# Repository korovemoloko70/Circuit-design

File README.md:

# Circuit-design
my projects for 2024-2025

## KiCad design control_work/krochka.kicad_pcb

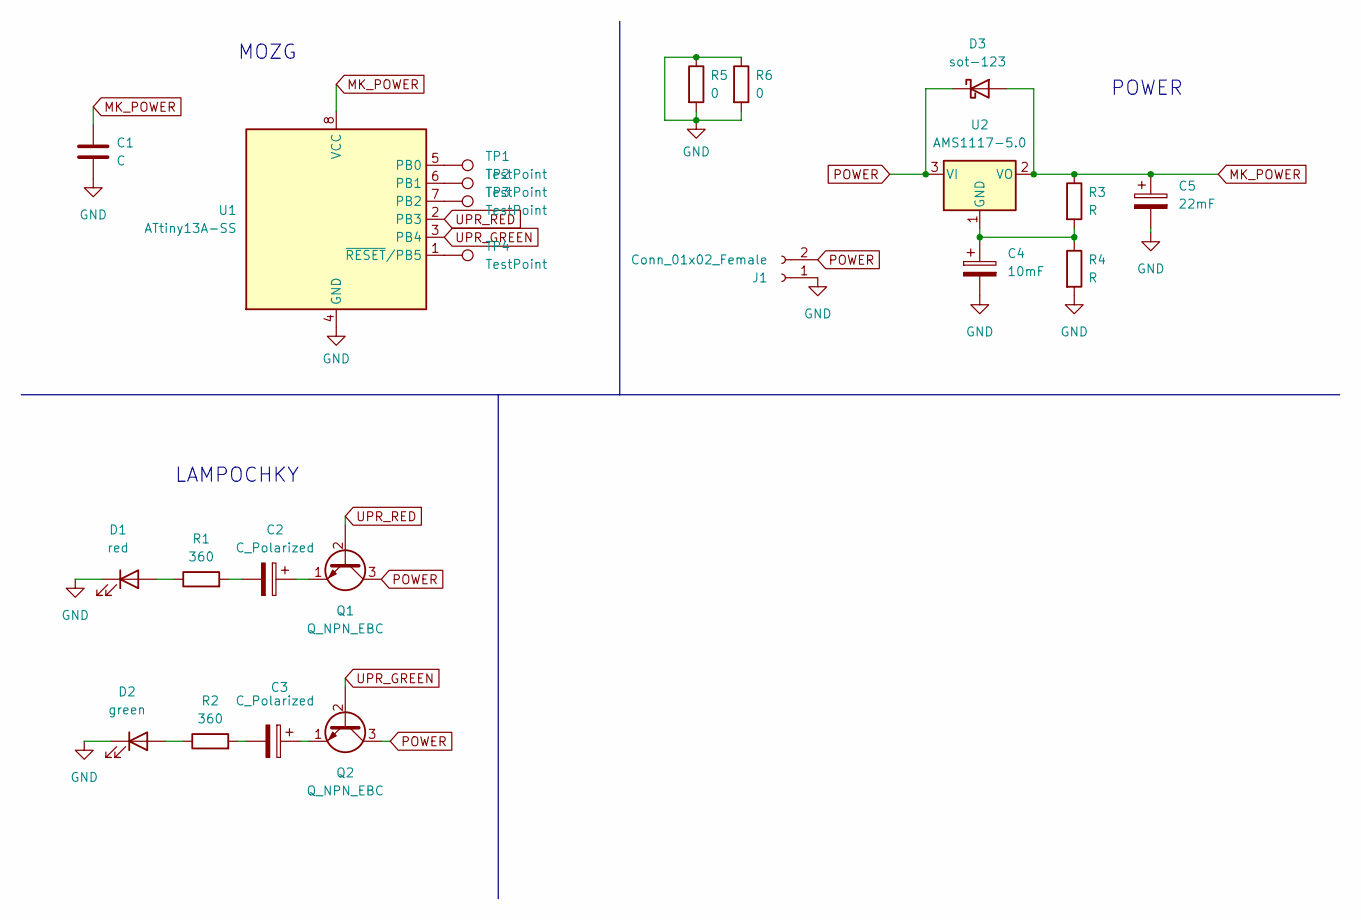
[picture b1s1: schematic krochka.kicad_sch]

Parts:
C1: C; CP_Elec_4x3
C2, C3: C_Polarized; CP_EIA-3528-21_Kemet-B
C4: 10mF; CP_EIA-3528-21_Kemet-B
C5: 22mF; CP_EIA-3528-21_Kemet-B
D1: red; LED_D5.0mm
D2: green; LED_D5.0mm
D3: sot-123; D_0201_0603Metric_Pad0.64x0.40mm_HandSolder
J1: Conn_01x02_Female; PinSocket_1x02_P2.00mm_Vertical
Q1, Q2: Q_NPN_EBC; SOT-23
R1, R2: 360; R_0402_1005Metric_Pad0.72x0.64mm_HandSolder
R3, R4: R; R_0402_1005Metric_Pad0.72x0.64mm_HandSolder
R5, R6: 0; R_0603_1608Metric
TP1, TP2, TP3, TP4: TestPoint; TestPoint_Pad_D1.5mm
U1: ATtiny13A-SS; SOIC-8_3.9x4.9mm_P1.27mm
U2: AMS1117-5.0; SOT-223-3_TabPin2

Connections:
GND: C1.2, C4.2, C5.2, D1.1 (K), D2.1 (K), J1.1, R4.2, R5.1, R5.2, R6.1, R6.2, U1.4 (GND)
MK_POWER: C1.1, C5.1, D3.2 (A), R3.1, U1.8 (VCC), U2.2 (VO)
unnamed: C2.1, Q1.1 (E)
unnamed: C2.2, R1.2
unnamed: C3.1, Q2.1 (E)
unnamed: C3.2, R2.2
unnamed: C4.1, R3.2, R4.1, U2.1 (GND)
unnamed: D1.2 (A), R1.1
unnamed: D2.2 (A), R2.1
unnamed: TP1.1, U1.5 (PB0)
unnamed: TP2.1, U1.6 (PB1)
unnamed: TP3.1, U1.7 (PB2)
unnamed: TP4.1, U1.1 (~RESET/PB5)
POWER: D3.1 (K), J1.2, Q1.3 (C), Q2.3 (C), U2.3 (VI)
UPR_GREEN: Q2.2 (B), U1.3 (PB4)
UPR_RED: Q1.2 (B), U1.2 (PB3)

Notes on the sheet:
POWER
MOZG
LAMPOCHKY

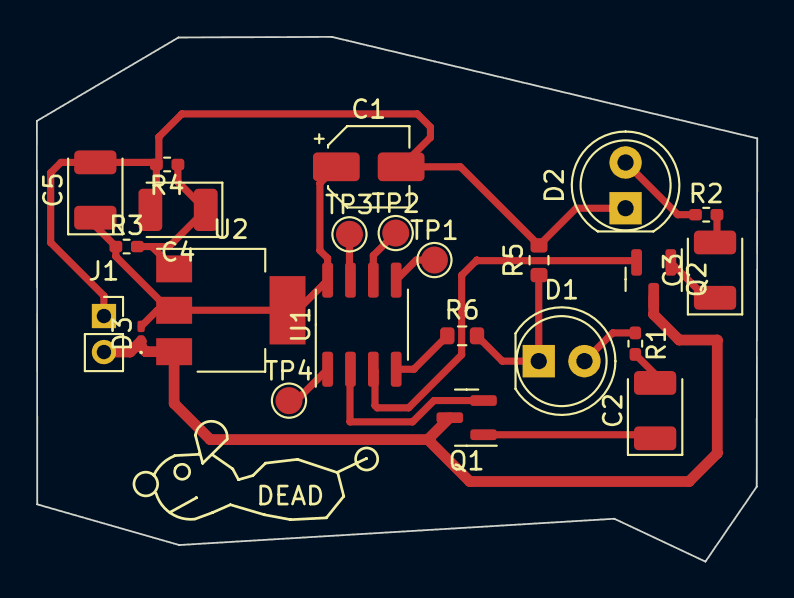
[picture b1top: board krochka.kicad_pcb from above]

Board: 2 copper layers, 40.0 x 29.2 mm, 23 parts (0 on the bottom side), 16 nets.

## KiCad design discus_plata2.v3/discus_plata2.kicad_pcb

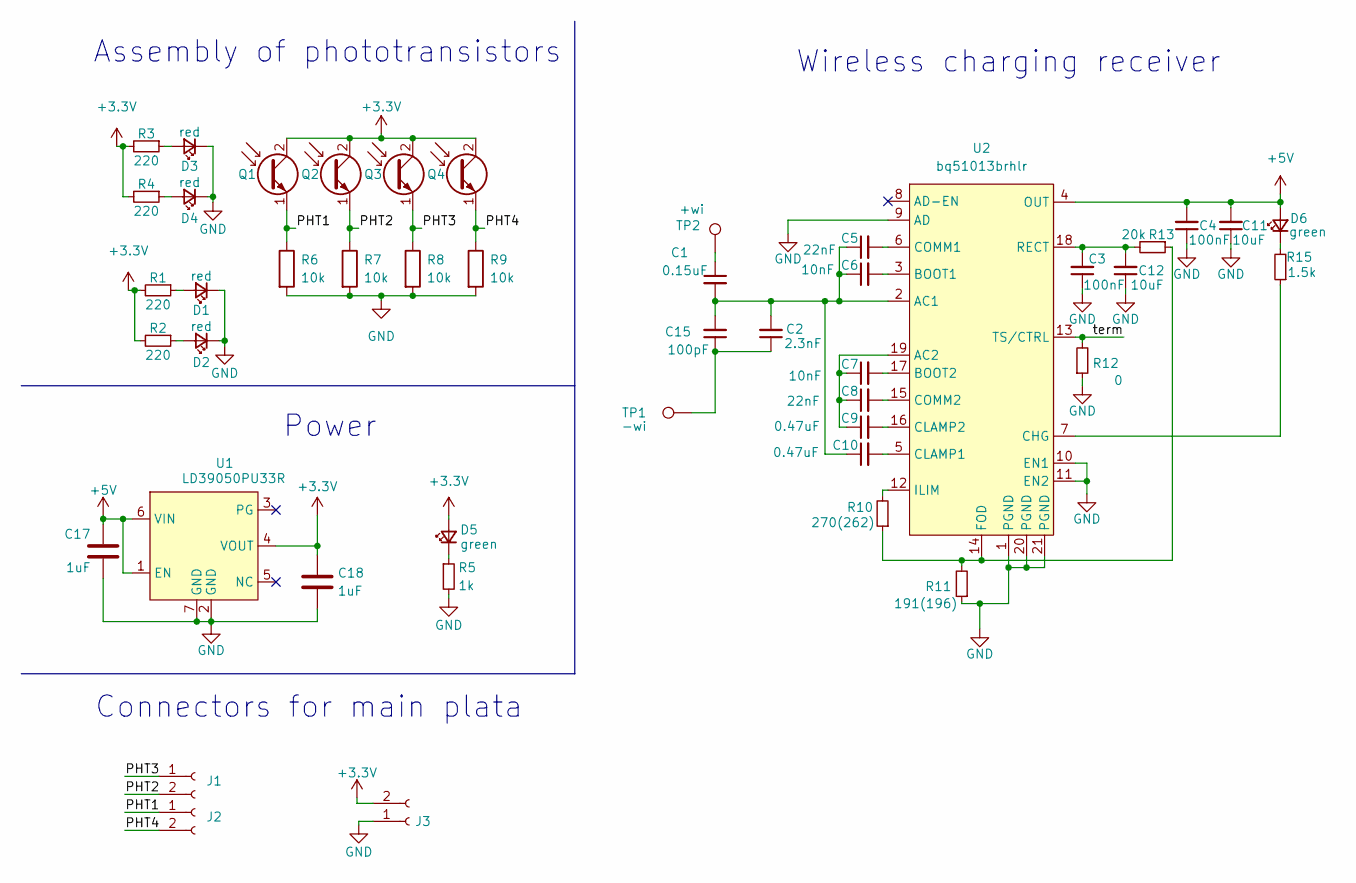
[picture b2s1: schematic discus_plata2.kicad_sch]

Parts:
C1: 0.15uF; C_0402_1005Metric_Pad0.74x0.62mm_HandSolder
C2: 2.3nF; C_0402_1005Metric_Pad0.74x0.62mm_HandSolder
C3, C4: 100nF; C_0201_0603Metric_Pad0.64x0.40mm_HandSolder
C5, C8: 22nF; C_0402_1005Metric_Pad0.74x0.62mm_HandSolder
C6, C7: 10nF; C_0402_1005Metric_Pad0.74x0.62mm_HandSolder
C9, C10: 0.47uF; C_0402_1005Metric_Pad0.74x0.62mm_HandSolder
C11, C12: 10uF; C_0402_1005Metric_Pad0.74x0.62mm_HandSolder
C15: 100pF; C_0402_1005Metric_Pad0.74x0.62mm_HandSolder
C17, C18: 1uF; C_0402_1005Metric_Pad0.74x0.62mm_HandSolder
D1, D2, D3, D4: red; LED_0603_1608Metric_Pad1.05x0.95mm_HandSolder
D5, D6: green; LED_0603_1608Metric_Pad1.05x0.95mm_HandSolder
J1, J2, J3: B2B-ZR
Q1, Q2, Q3, Q4: Q_Photo_NPN_EC; R_1206_3216Metric_Pad1.30x1.75mm_HandSolder
R1, R2, R3, R4: 220; R_0603_1608Metric_Pad0.98x0.95mm_HandSolder
R5: 1k; R_0402_1005Metric_Pad0.72x0.64mm_HandSolder
R6, R7, R8, R9: 10k; R_0402_1005Metric_Pad0.72x0.64mm_HandSolder
R10: 270(262); R_0402_1005Metric_Pad0.72x0.64mm_HandSolder
R11: 191(196); R_0402_1005Metric_Pad0.72x0.64mm_HandSolder
R12: 0; R_0201_0603Metric_Pad0.64x0.40mm_HandSolder
R13: 20k; R_0402_1005Metric_Pad0.72x0.64mm_HandSolder
R15: 1.5k; R_0402_1005Metric_Pad0.72x0.64mm_HandSolder
TP1: -wi; WICH_TESTP
TP2: +wi; WICH_TESTP
U1: LD39050PU33R; DFN-6-1EP_3x3mm_P0.95mm_EP1.7x2.6mm
U2: bq51013brhlr; Texas_VQFN-RHL-20

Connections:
+3.3V: C18.1, D5.2 (A), J3.2, Q1.2 (C), Q2.2 (C), Q3.2 (C), Q4.2 (C), R1.2, R2.2, R3.2, R4.2, U1.4 (VOUT)
+5V: C4.2, C11.2, C17.1, D6.2 (A), U1.1 (EN), U1.6 (VIN), U2.4 (OUT)
/PHT1: J2.1, Q1.1 (E), R6.1
/PHT2: J1.2, Q2.1 (E), R7.1
/PHT3: J1.1, Q3.1 (E), R8.1
/PHT4: J2.2, Q4.1 (E), R9.1
/term: R12.2, U2.13 (TS/CTRL)
GND: C3.1, C4.1, C11.1, C12.1, C17.2, C18.2, D1.1 (K), D2.1 (K), D3.1 (K), D4.1 (K), J3.1, R5.2, R6.2, R7.2, R8.2, R9.2, R11.1, R12.1, U1.2 (GND), U1.7 (GND), U2.1 (PGND), U2.9 (AD), U2.10 (EN1), U2.11 (EN2), U2.20 (PGND), U2.21 (PGND)
unnamed: C1.1, TP2.1
unnamed: C2.1, C15.1, TP1.1
unnamed: D1.2 (A), R1.1
unnamed: D2.2 (A), R2.1
unnamed: D3.2 (A), R3.1
unnamed: D4.2 (A), R4.1
unnamed: D5.1 (K), R5.1
unnamed: D6.1 (K), R15.2
unnamed: C1.2, C2.2, C5.1, C6.1, C10.1, C15.2, U2.2 (AC1)
unnamed: C7.1, C8.1, C9.1, U2.19 (AC2)
unnamed: C6.2, U2.3 (BOOT1)
unnamed: C7.2, U2.17 (BOOT2)
unnamed: R15.1, U2.7 (CHG)
unnamed: C10.2, U2.5 (CLAMP1)
unnamed: C9.2, U2.16 (CLAMP2)
unnamed: C5.2, U2.6 (COMM1)
unnamed: C8.2, U2.15 (COMM2)
unnamed: R10.1, R11.2, R13.1, U2.14 (FOD)
unnamed: R10.2, U2.12 (ILIM)
unnamed: C3.2, C12.2, R13.2, U2.18 (RECT)

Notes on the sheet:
Connectors for main plata
Assembly of phototransistors
Wireless charging receiver
Power

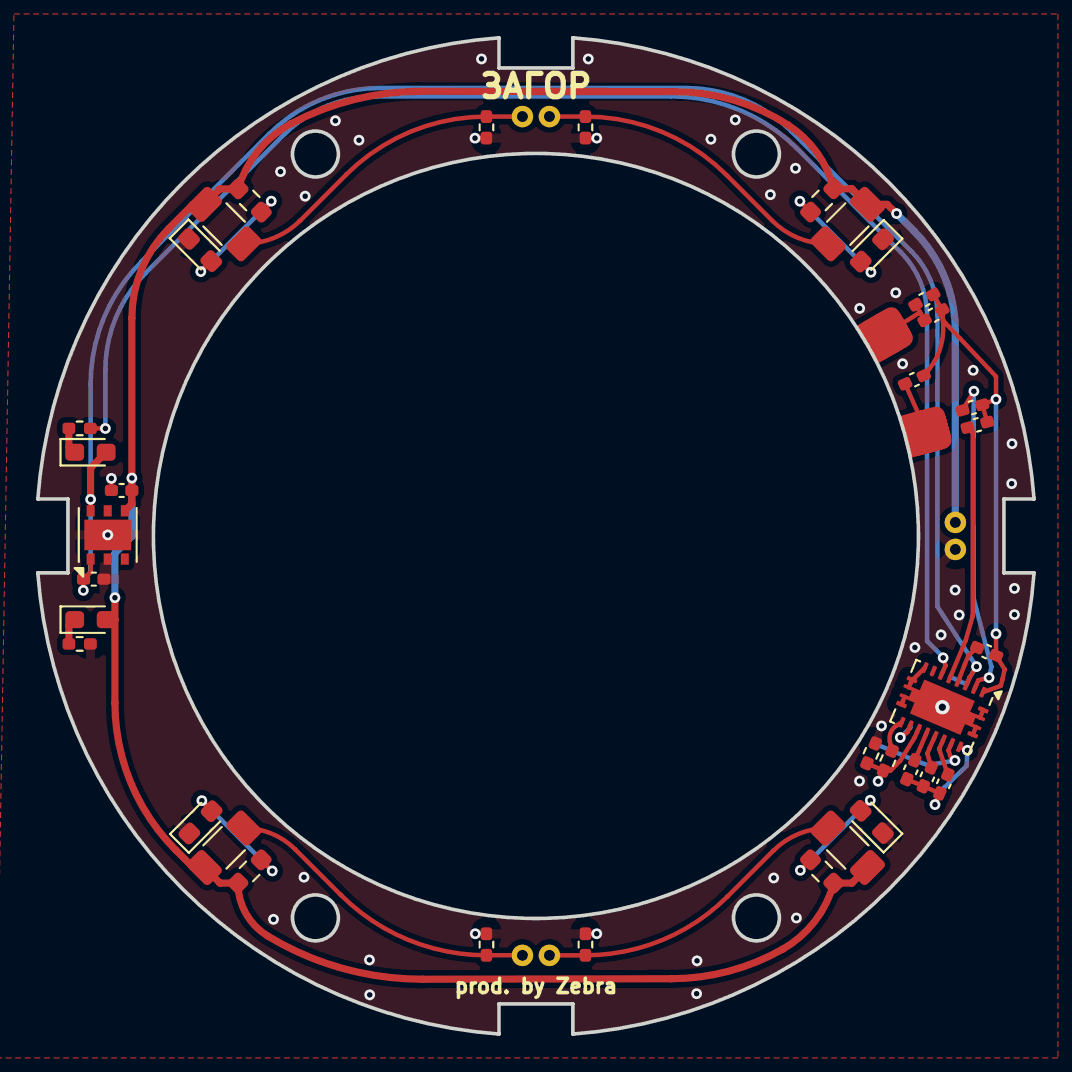
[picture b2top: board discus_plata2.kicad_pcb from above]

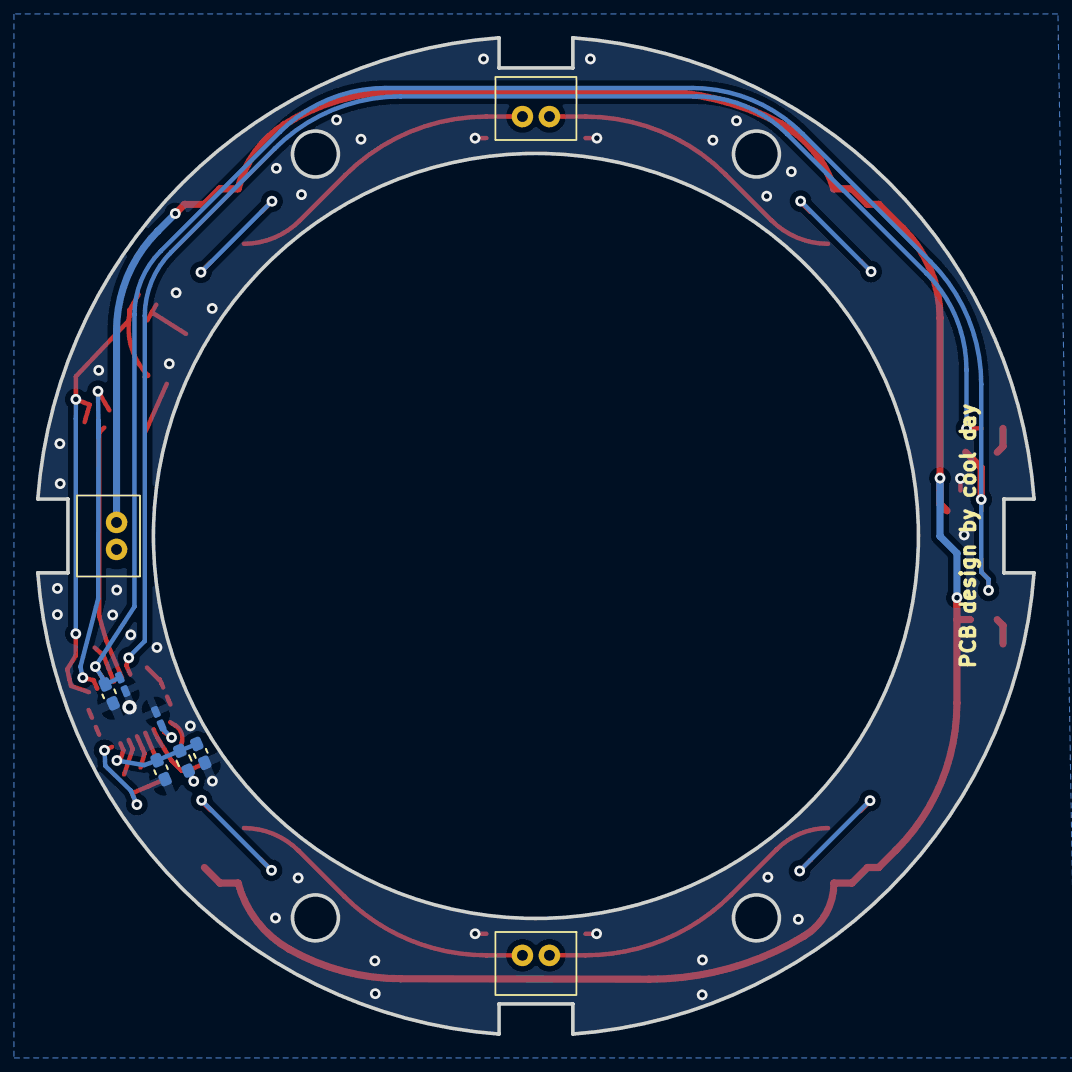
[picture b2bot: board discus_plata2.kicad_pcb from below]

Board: 2 copper layers, 55.3 x 55.3 mm, 46 parts (9 on the bottom side), 28 nets.

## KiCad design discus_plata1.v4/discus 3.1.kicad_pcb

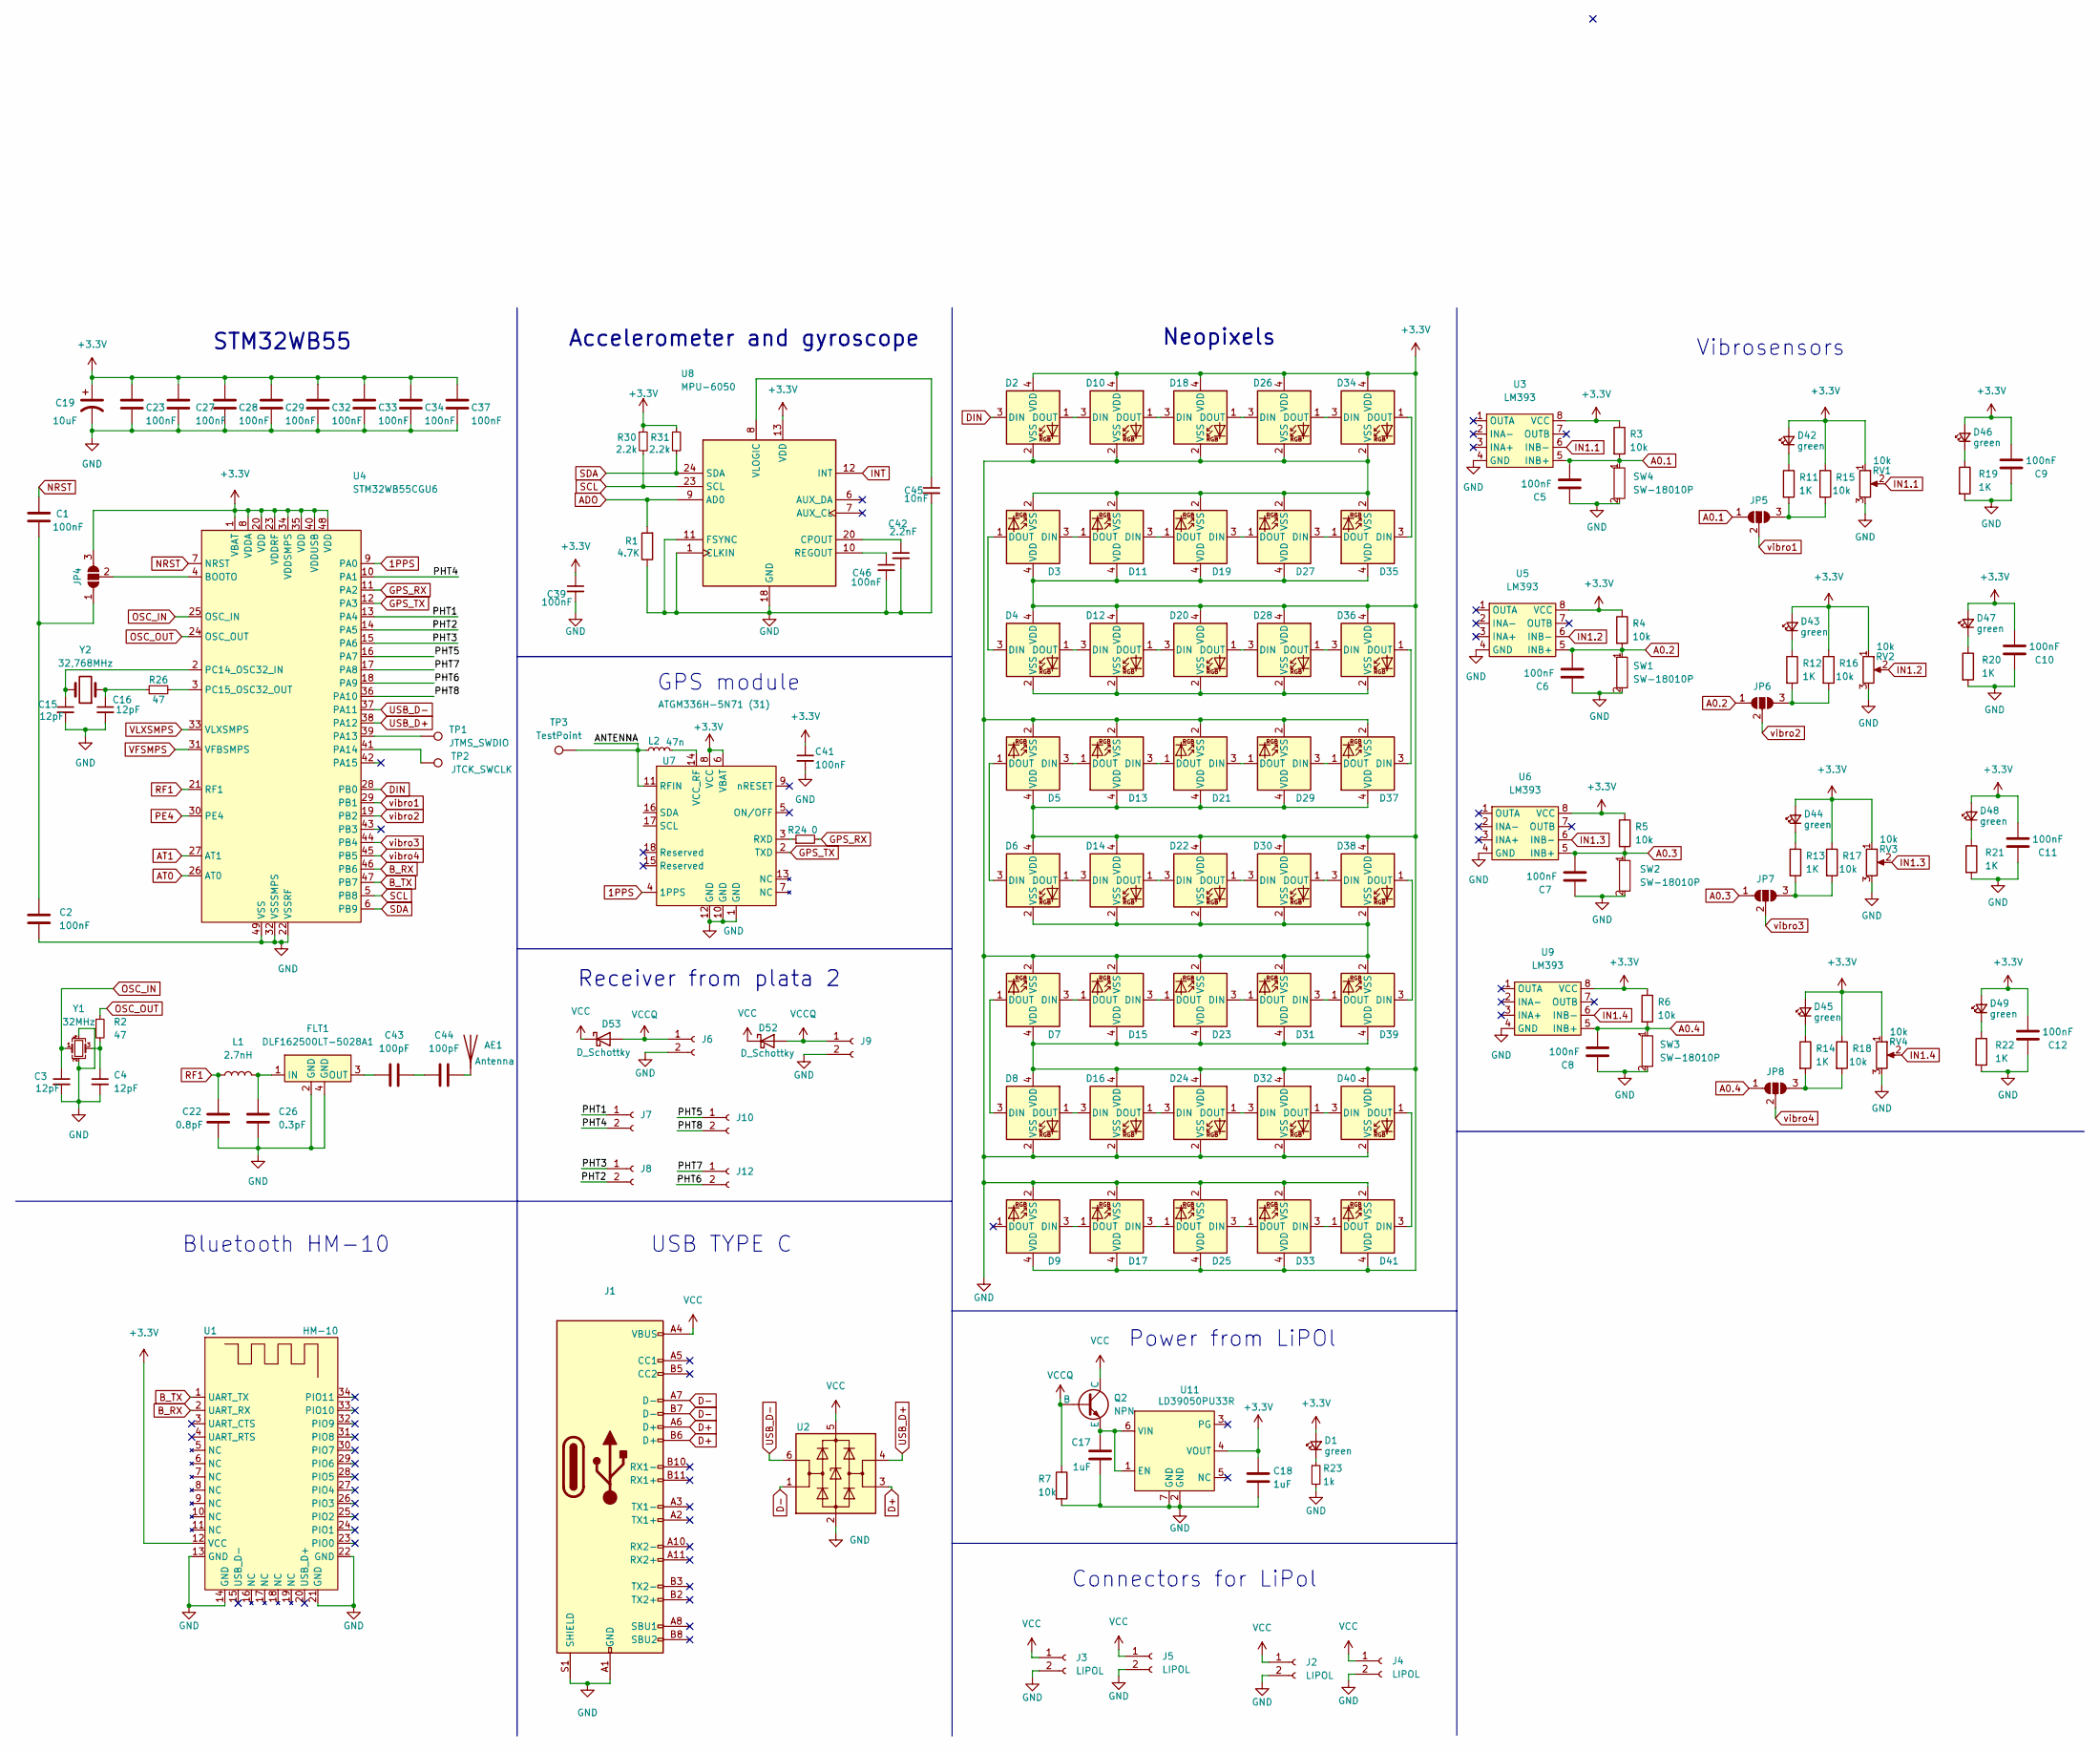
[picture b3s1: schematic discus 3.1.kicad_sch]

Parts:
AE1: Antenna; ANTENNA
C1, C2, C5, C6, C7, C8, C9, C10, C11, C12, C23, C27, C28, C29, C32, C33, C34, C37, C39, C41, C46: 100nF; C_0603_1608Metric_Pad1.08x0.95mm_HandSolder
C3, C4, C15, C16: 12pF; C_0603_1608Metric_Pad1.08x0.95mm_HandSolder
C17, C18: 1uF; C_0402_1005Metric_Pad0.74x0.62mm_HandSolder
C19: 10uF; CP_EIA-3216-18_Kemet-A_HandSolder
C22: 0.8pF; C_0603_1608Metric_Pad1.08x0.95mm_HandSolder
C26: 0.3pF; C_0603_1608Metric_Pad1.08x0.95mm_HandSolder
C42: 2.2nF; C_0603_1608Metric_Pad1.08x0.95mm_HandSolder
C43, C44: 100pF; C_0603_1608Metric_Pad1.08x0.95mm_HandSolder
C45: 10nF; C_0603_1608Metric_Pad1.08x0.95mm_HandSolder
D1, D42, D43, D44, D45, D46, D47, D48, D49: green; LED_0603_1608Metric_Pad1.05x0.95mm_HandSolder
D2, D3, D4, D5, D6, D7, D8, D9, D10, D11, D12, D13, D14, D15, D16, D17, D18, D19, D20, D21, D22, D23, D24, D25, D26, D27, D28, D29, D30, D31, D32, D33, D34, D35, D36, D37, D38, D39, D40, D41: WS2812B; led
D52, D53: D_Schottky; D_SOD-123
FLT1: DLF162500LT-5028A1; FLT1
J1: USB_C_Receptacle_G-Switch_GT-USB-7010ASV
J2, J3, J4, J5: LIPOL; B2B-ZR
J6, J7, J8, J9, J10, J12: Conn_01x02_Socket; B2B-ZR
JP4, JP5, JP6, JP7, JP8: SolderJumper_3_Open; SolderJumper-3_P1.3mm_Open_RoundedPad1.0x1.5mm
L1: 2.7nH; L_0805_2012Metric_Pad1.05x1.20mm_HandSolder
L2: 47n; L_0603_1608Metric_Pad1.05x0.95mm_HandSolder
Q2: NPN; SOT-23
R1: 4.7K; R_0603_1608Metric_Pad0.98x0.95mm_HandSolder
R2, R26: 47; R_0603_1608Metric_Pad0.98x0.95mm_HandSolder
R3, R4, R5, R6, R7, R15, R16, R17, R18: 10k; R_0603_1608Metric_Pad0.98x0.95mm_HandSolder
R11, R12, R13, R14, R19, R20, R21, R22: 1K; R_0603_1608Metric_Pad0.98x0.95mm_HandSolder
R23: 1k; R_0603_1608Metric_Pad0.98x0.95mm_HandSolder
R24: 0; R_0603_1608Metric_Pad0.98x0.95mm_HandSolder
R30, R31: 2.2k; R_0603_1608Metric_Pad0.98x0.95mm_HandSolder
RV1, RV2, RV3, RV4: 10k; Trimming Potentiometr
SW1, SW2, SW3, SW4: SW-18010P; SW1810-P
TP1: JTMS_SWDIO; TestPoint_Pad_D2.0mm
TP2: JTCK_SWCLK; TestPoint_Pad_D2.0mm
TP3: TestPoint; U.FL_Hirose_U.FL-R-SMT-1_Vertical
U1: HM-10
U2: USBLC6-2P6; SOT-563
U3, U5, U6, U9: LM393
U4: STM32WB55CGU6; QFN-48-1EP_7x7mm_P0.5mm_EP5.6x5.6mm
U7: ATGM336H-5N71 (31); ATGM336H-5N
U8: MPU-6050; InvenSense_QFN-24_4x4mm_P0.5mm
U11: LD39050PU33R; DFN-6-1EP_3x3mm_P0.95mm_EP1.7x2.6mm
Y1: 32MHz; Crystal_SMD_3225-4Pin_3.2x2.5mm
Y2: 32,768MHz; Crystal_SMD_3215-2Pin_3.2x1.5mm

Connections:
1PPS: U4.9 (PA0), U7.4 (1PPS)
+3.3V: C9.2, C10.2, C11.2, C12.2, C18.1, C19.1, C23.1, C27.1, C28.1, C29.1, C32.1, C33.1, C34.1, C37.1, C39.1, C41.1, D1.2 (A), D2.4 (VDD), D3.4 (VDD), D4.4 (VDD), D5.4 (VDD), D6.4 (VDD), D7.4 (VDD), D8.4 (VDD), D9.4 (VDD), D10.4 (VDD), D11.4 (VDD), D12.4 (VDD), D13.4 (VDD), D14.4 (VDD), D15.4 (VDD), D16.4 (VDD), D17.4 (VDD), D18.4 (VDD), D19.4 (VDD), D20.4 (VDD), D21.4 (VDD), D22.4 (VDD), D23.4 (VDD), D24.4 (VDD), D25.4 (VDD), D26.4 (VDD), D27.4 (VDD), D28.4 (VDD), D29.4 (VDD), D30.4 (VDD), D31.4 (VDD), D32.4 (VDD), D33.4 (VDD), D34.4 (VDD), D35.4 (VDD), D36.4 (VDD), D37.4 (VDD), D38.4 (VDD), D39.4 (VDD), D40.4 (VDD), D41.4 (VDD), D42.2 (A), D43.2 (A), D44.2 (A), D45.2 (A), D46.2 (A), D47.2 (A), D48.2 (A), D49.2 (A), JP4.3 (B), R3.1, R4.1, R5.1, R6.1, R15.1, R16.1, R17.1, R18.1, R30.1, R31.1, RV1.1, RV2.1, RV3.1, RV4.1, U1.12 (VCC), U3.8 (VCC), U4.1 (VBAT), U4.8 (VDDA), U4.20 (VDD), U4.23 (VDDRF), U4.34 (VDDSMPS), U4.35 (VDD), U4.40 (VDDUSB), U4.48 (VDD), U5.8 (VCC), U6.8 (VCC), U7.6 (VBAT), U7.8 (VCC), U8.13 (VDD), U9.8 (VCC), U11.4 (VOUT)
/ANTENNA: L2.1, TP3.1, U7.11 (RFIN)
/PHT1: J7.1, U4.13 (PA4)
/PHT2: J8.2, U4.14 (PA5)
/PHT3: J8.1, U4.15 (PA6)
/PHT4: J7.2, U4.10 (PA1)
/PHT5: J10.1, U4.16 (PA7)
/PHT6: J12.2, U4.18 (PA9)
/PHT7: J12.1, U4.17 (PA8)
/PHT8: J10.2, U4.36 (PA10)
A0.1: C5.2, JP5.1 (A), R3.2, SW4.1, U3.5 (INB+)
A0.2: C6.2, JP6.1 (A), R4.2, SW1.1, U5.5 (INB+)
A0.3: C7.2, JP7.1 (A), R5.2, SW2.1, U6.5 (INB+)
A0.4: C8.2, JP8.1 (A), R6.2, SW3.1, U9.5 (INB+)
ADO: R1.2, U8.9 (AD0)
AT0: U4.26 (AT0)
AT1: U4.27 (AT1)
B_RX: U1.2 (UART_RX), U4.46 (PB6)
B_TX: U1.1 (UART_TX), U4.47 (PB7)
D+: J1.A6 (D+), J1.B6 (D+), U2.3 (I/O2)
D-: J1.A7 (D-), J1.B7 (D-), U2.1 (I/O1)
DIN: D2.3 (DIN), U4.28 (PB0)
GPS_RX: R24.2, U4.11 (PA2)
GPS_TX: U4.12 (PA3), U7.2 (TXD)
IN1.1: RV1.2, U3.6 (INB-)
IN1.2: RV2.2, U5.6 (INB-)
IN1.3: RV3.2, U6.6 (INB-)
IN1.4: RV4.2, U9.6 (INB-)
INT: U8.12 (INT)
NRST: C1.1, U4.7 (NRST)
unnamed: AE1.1 (A), C44.2
unnamed: C4.1, R2.2, Y1.3
unnamed: C16.1, R26.1, Y2.1
unnamed: C43.2, C44.1
unnamed: D1.1 (K), R23.1
unnamed: D3.1 (DOUT), D4.3 (DIN)
unnamed: D5.1 (DOUT), D6.3 (DIN)
unnamed: D7.1 (DOUT), D8.3 (DIN)
unnamed: D2.1 (DOUT), D10.3 (DIN)
unnamed: D10.1 (DOUT), D18.3 (DIN)
unnamed: D11.3 (DIN), D19.1 (DOUT)
unnamed: D3.3 (DIN), D11.1 (DOUT)
unnamed: D4.1 (DOUT), D12.3 (DIN)
unnamed: D12.1 (DOUT), D20.3 (DIN)
unnamed: D13.3 (DIN), D21.1 (DOUT)
unnamed: D5.3 (DIN), D13.1 (DOUT)
unnamed: D6.1 (DOUT), D14.3 (DIN)
unnamed: D14.1 (DOUT), D22.3 (DIN)
unnamed: D15.3 (DIN), D23.1 (DOUT)
unnamed: D7.3 (DIN), D15.1 (DOUT)
unnamed: D8.1 (DOUT), D16.3 (DIN)
unnamed: D16.1 (DOUT), D24.3 (DIN)
unnamed: D17.3 (DIN), D25.1 (DOUT)
unnamed: D9.3 (DIN), D17.1 (DOUT)
unnamed: D18.1 (DOUT), D26.3 (DIN)
unnamed: D19.3 (DIN), D27.1 (DOUT)
unnamed: D20.1 (DOUT), D28.3 (DIN)
unnamed: D21.3 (DIN), D29.1 (DOUT)
unnamed: D22.1 (DOUT), D30.3 (DIN)
unnamed: D23.3 (DIN), D31.1 (DOUT)
unnamed: D24.1 (DOUT), D32.3 (DIN)
unnamed: D25.3 (DIN), D33.1 (DOUT)
unnamed: D26.1 (DOUT), D34.3 (DIN)
unnamed: D27.3 (DIN), D35.1 (DOUT)
unnamed: D28.1 (DOUT), D36.3 (DIN)
unnamed: D29.3 (DIN), D37.1 (DOUT)
unnamed: D30.1 (DOUT), D38.3 (DIN)
unnamed: D31.3 (DIN), D39.1 (DOUT)
unnamed: D32.1 (DOUT), D40.3 (DIN)
unnamed: D33.3 (DIN), D41.1 (DOUT)
unnamed: D34.1 (DOUT), D35.3 (DIN)
unnamed: D36.1 (DOUT), D37.3 (DIN)
unnamed: D38.1 (DOUT), D39.3 (DIN)
unnamed: D40.1 (DOUT), D41.3 (DIN)
unnamed: D42.1 (K), R11.1
unnamed: D43.1 (K), R12.1
unnamed: D44.1 (K), R13.1
unnamed: D45.1 (K), R14.1
unnamed: D46.1 (K), R19.1
unnamed: D47.1 (K), R20.1
unnamed: D48.1 (K), R21.1
unnamed: D49.1 (K), R22.1
unnamed: C26.1, FLT1.1 (IN), L1.2
unnamed: C43.1, FLT1.3 (OUT)
unnamed: C1.2, C2.1, JP4.1 (A)
unnamed: JP4.2 (C), U4.4 (BOOTO)
unnamed: JP5.3 (B), R11.2, R15.2
unnamed: JP6.3 (B), R12.2, R16.2
unnamed: JP7.3 (B), R13.2, R17.2
unnamed: JP8.3 (B), R14.2, R18.2
unnamed: C17.1, Q2.3 (E), U11.1 (EN), U11.6 (VIN)
unnamed: TP1.1, U4.39 (PA13)
unnamed: TP2.1, U4.41 (PA14)
unnamed: C15.1, U4.2 (PC14_OSC32_IN), Y2.2
unnamed: R26.2, U4.3 (PC15_OSC32_OUT)
unnamed: R24.1, U7.3 (RXD)
unnamed: L2.2, U7.14 (VCC_RF)
unnamed: C42.1, U8.20 (CPOUT)
unnamed: C46.1, U8.10 (REGOUT)
unnamed: C45.1, U8.8 (VLOGIC)
OSC_IN: C3.1, U4.25 (OSC_IN), Y1.1
OSC_OUT: R2.1, U4.24 (OSC_OUT)
PE4: U4.30 (PE4)
RF1: C22.1, L1.1, U4.21 (RF1)
SCL: R30.2, U4.5 (PB8), U8.23 (SCL)
SDA: R31.2, U4.6 (PB9), U8.24 (SDA)
USB_D+: U2.4 (I/O2), U4.38 (PA12)
USB_D-: U2.6 (I/O1), U4.37 (PA11)
VCC: D52.1 (K), D53.1 (K), J1.A4 (VBUS), J1.A9 (VBUS), J1.B4 (VBUS), J1.B9 (VBUS), J2.1, J3.1, J4.1, J5.1, Q2.1 (C), U2.5 (VBUS)
VCCQ: D52.2 (A), D53.2 (A), J6.1, J9.1, Q2.2 (B), R7.1
VFSMPS: U4.31 (VFBSMPS)
VLXSMPS: U4.33 (VLXSMPS)
vibro1: JP5.2 (C), U4.29 (PB1)
vibro2: JP6.2 (C), U4.19 (PB2)
vibro3: JP7.2 (C), U4.44 (PB4)
vibro4: JP8.2 (C), U4.45 (PB5)

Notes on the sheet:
Power from LiPOl
Accelerometer and gyroscope
Neopixels
USB TYPE C
Bluetooth HM-10
Receiver from plata 2
Vibrosensors
STM32WB55
Connectors for LiPol
GPS module

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
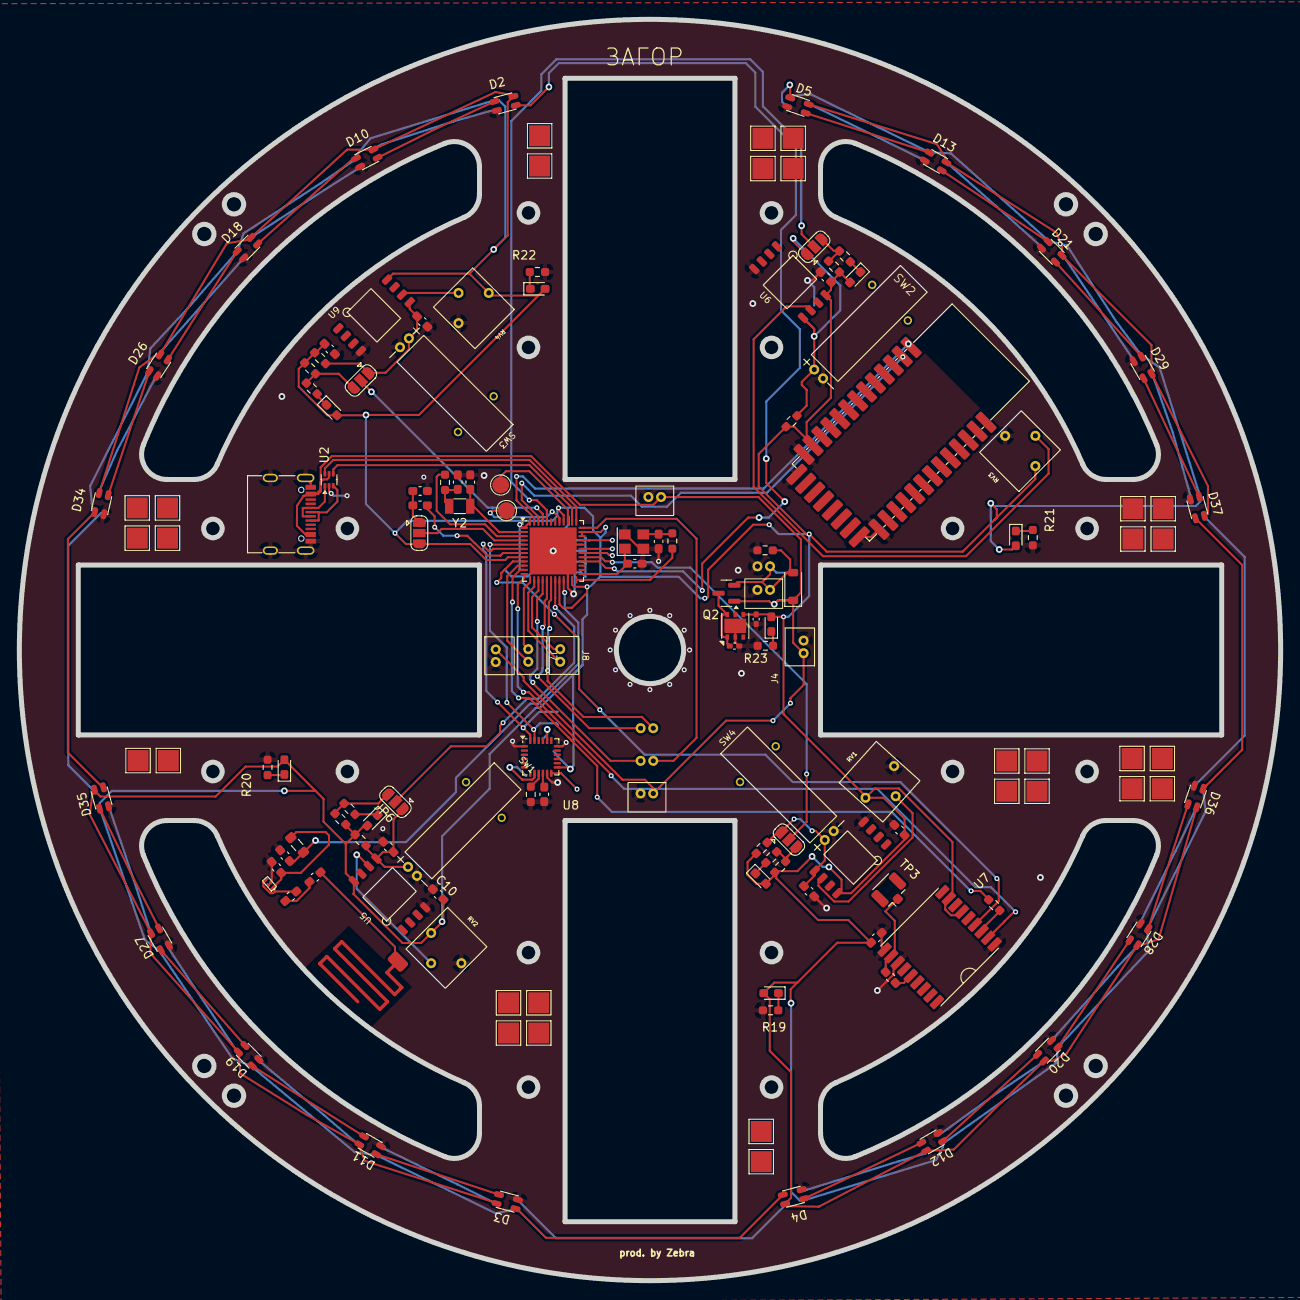
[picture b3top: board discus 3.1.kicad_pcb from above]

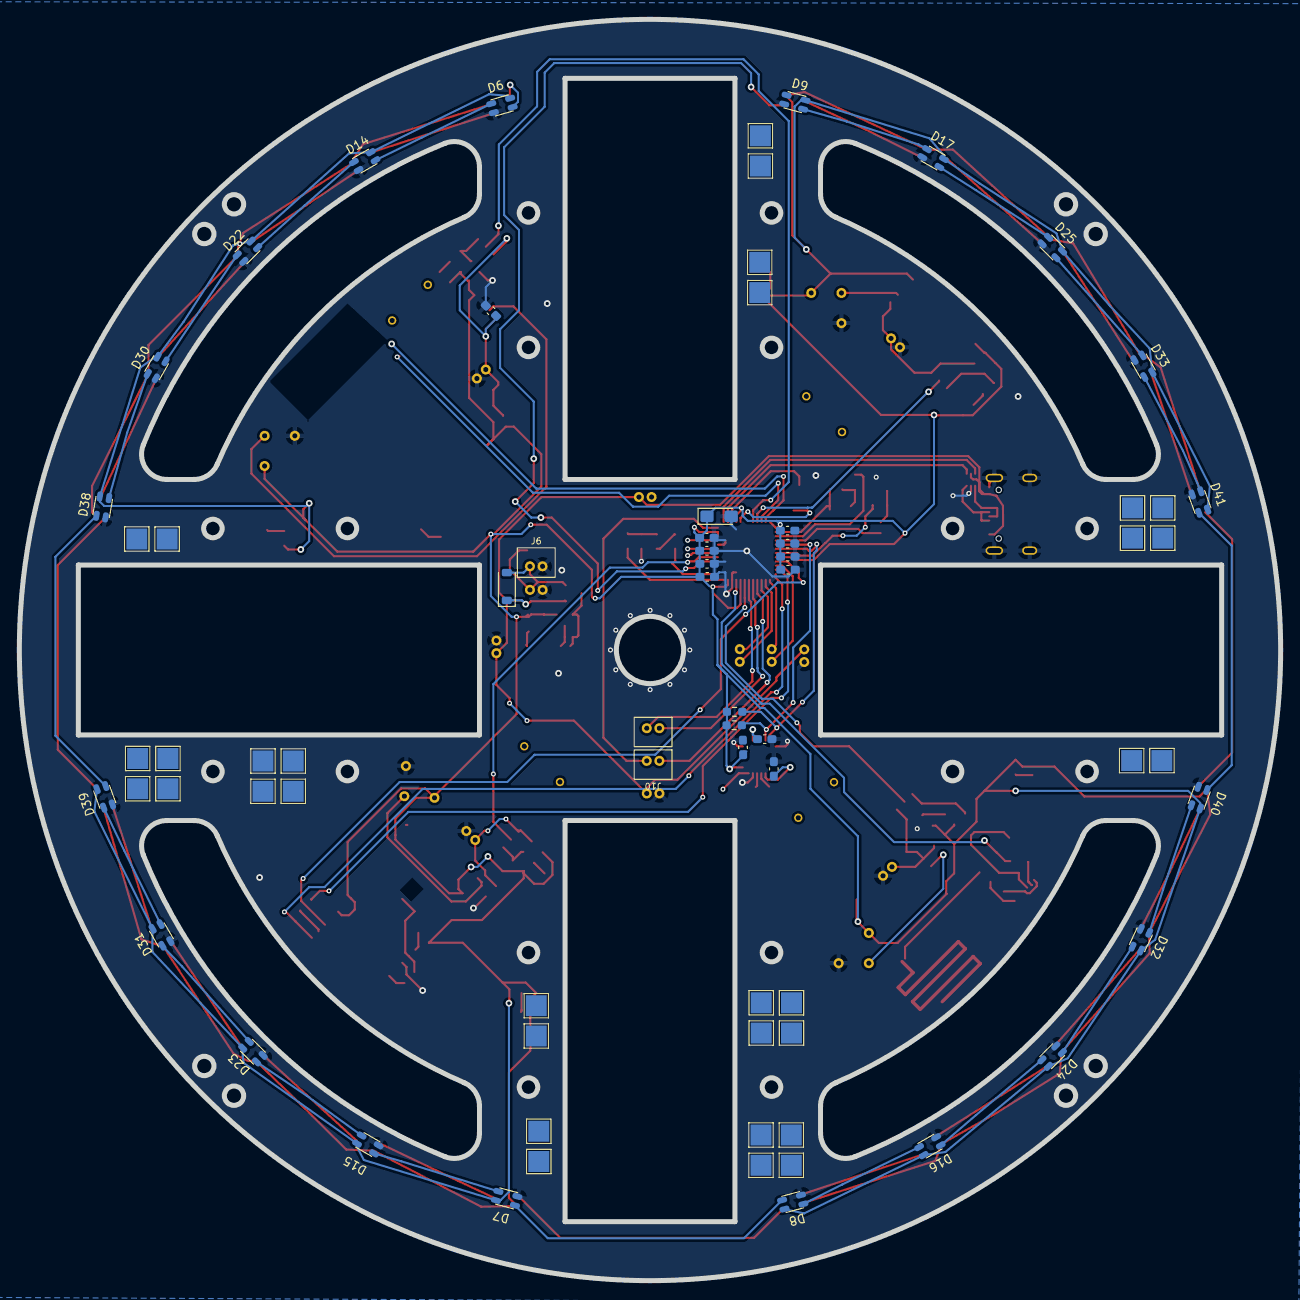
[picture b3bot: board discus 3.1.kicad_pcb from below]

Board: 2 copper layers, 150.0 x 150.0 mm, 153 parts (39 on the bottom side), 112 nets.
